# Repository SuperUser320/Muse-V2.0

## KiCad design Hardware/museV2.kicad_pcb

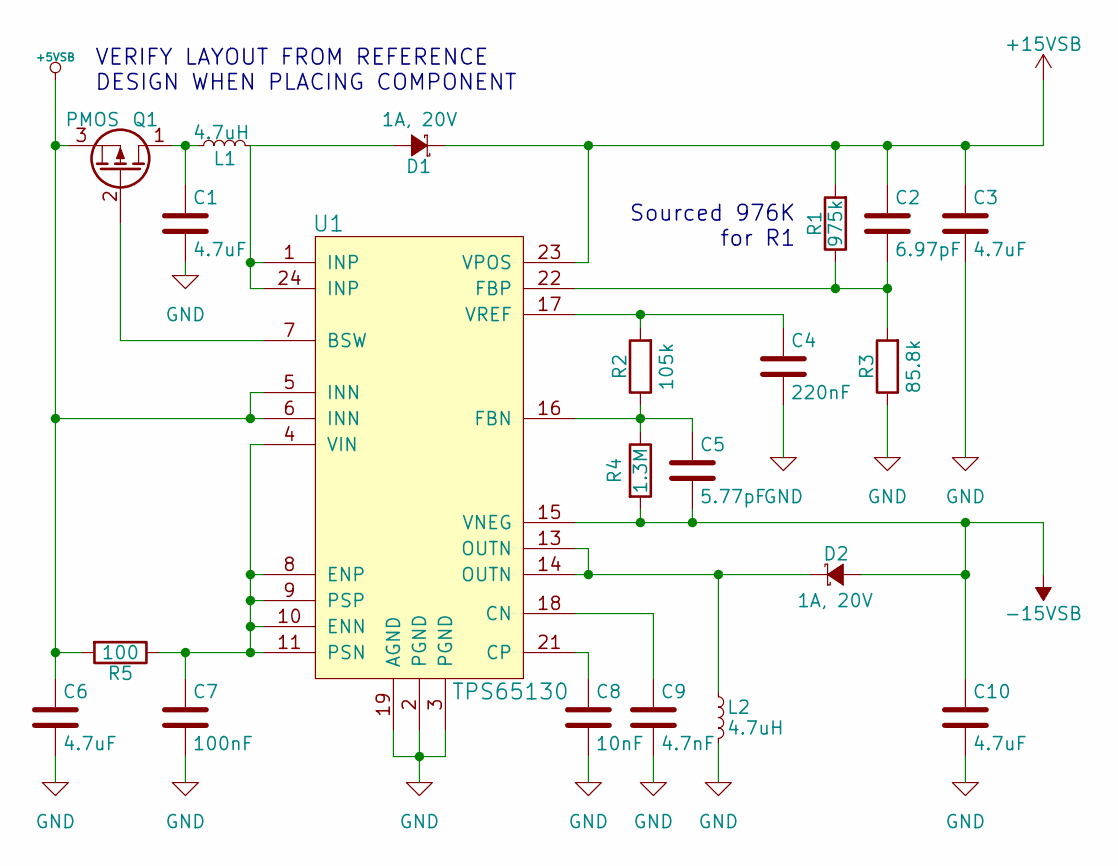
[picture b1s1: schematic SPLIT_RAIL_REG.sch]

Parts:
C1, C6: 4.7uF; C_0603
C2: 6.97pF; C_0402
C3, C10: 4.7uF; C_1206
C4: 220nF; C_0603
C5: 5.77pF; C_0603
C7: 100nF; C_0603
C8: 10nF; C_0603
C9: 4.7nF; C_0603
D1, D2: 1A, 20V; DO-216-AA
L1, L2: 4.7uH; 7.3mm-Inductor
Q1: PMOS; SOT-23
R1: 975k; R_0402
R2: 105k; R_0402
R3: 85.8k; R_0402
R4: 1.3M; R_0402
R5: 100; R_0402
U1: TPS65130; QFN-24-1EP_4x4mm_Pitch0.5mm_THERMAL

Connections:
+5VSB: C6.1, Q1.3 (S), R5.2, U1.5 (INN), U1.6 (INN); also elsewhere on the board
+15V: C2.1, C3.1, D1.1 (K), R1.2, U1.23 (VPOS); also elsewhere on the board
-15V: C5.2, C10.1, D2.2 (A), R4.2, U1.15 (VNEG); also elsewhere on the board
GND: C1.2, C3.2, C4.2, C6.2, C7.2, C8.2, C9.2, C10.2, L2.2, R3.1, U1.2 (PGND), U1.3 (PGND), U1.19 (AGND); also elsewhere on the board
unnamed: C1.1, L1.1, Q1.1 (D)
unnamed: C2.2, R1.1, R3.2, U1.22 (FBP)
unnamed: C4.1, R2.2, U1.17 (VREF)
unnamed: C5.1, R2.1, R4.1, U1.16 (FBN)
unnamed: C7.1, R5.1, U1.4 (VIN), U1.8 (ENP), U1.9 (PSP), U1.10 (ENN), U1.11 (PSN)
unnamed: C8.1, U1.21 (CP)
unnamed: C9.1, U1.18 (CN)
unnamed: D1.2 (A), L1.2, U1.1 (INP), U1.24 (INP)
unnamed: D2.1 (K), L2.1, U1.13 (OUTN), U1.14 (OUTN)
unnamed: Q1.2 (G), U1.7 (BSW)

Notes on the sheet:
VERIFY LAYOUT FROM REFERENCE DESIGN WHEN PLACING COMPONENT
Sourced 976K for R1

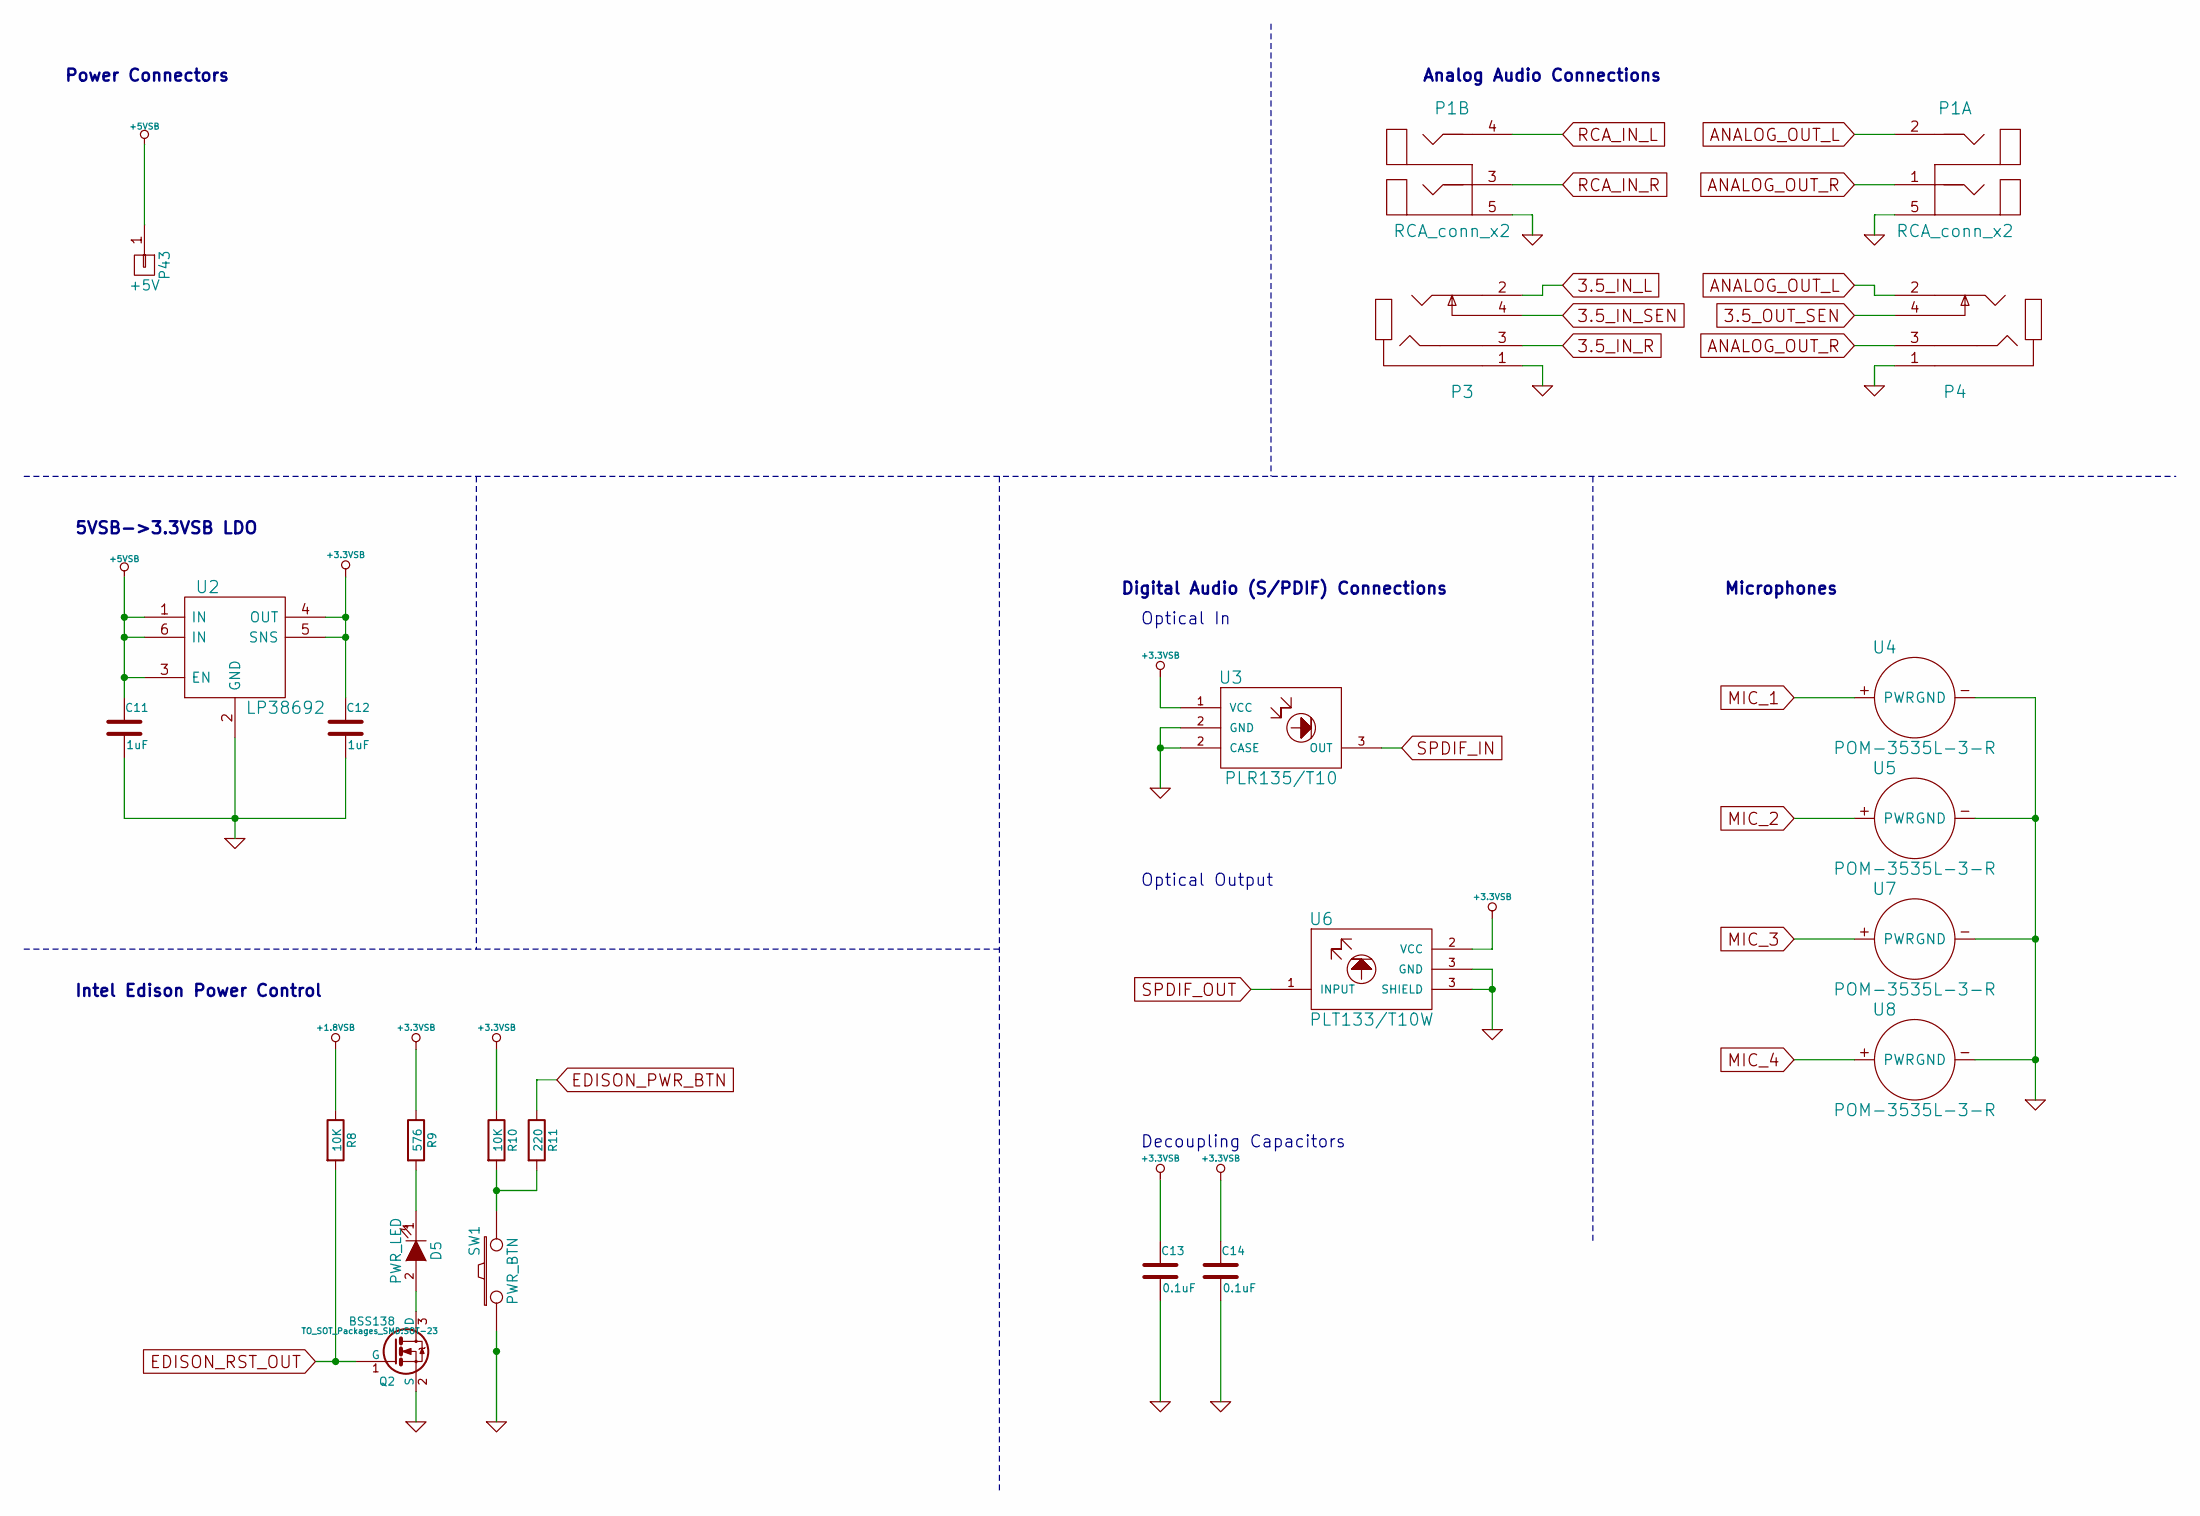
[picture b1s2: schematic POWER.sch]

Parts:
C11, C12: 1uF; C_0402
C13, C14: 0.1uF; C_0402
D5: PWR_LED; LED_0805
P1: RCA_conn_x2; PJRAS2X2S01X
P3, P4: 3.5mm_conn_tip_switch; 3.5MM-AUDIO-SMD
P43: +5V; Pin_Header_Straight_1x01
Q2: BSS138; SOT-23
R8, R10: 10K; R_0402
R9: 576; R_0402
R11: 220; R_0402
SW1: PWR_BTN; MF_Switches-TACT4.2MM
U2: LP38692; WSON6
U3: PLR135/T10; PLT133-T10W
U4, U5, U7, U8: POM-3535L-3-R; Pin_Header_Straight_1x02_MIC
U6: PLT133/T10W; PLT133-T10W

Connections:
3.5_IN_L: P3.2; also elsewhere on the board
3.5_IN_R: P3.3; also elsewhere on the board
3.5_IN_SEN: P3.4
3.5_OUT_SEN: P4.4
+1.8VSB: R8.1; also elsewhere on the board
+3.3VSB: C12.1, C13.1, C14.1, R9.1, R10.1, U2.4 (OUT), U2.5 (SNS), U3.1 (VCC), U6.2 (VCC); also elsewhere on the board
+5VSB: C11.1, P43.1, U2.1 (IN), U2.3 (EN), U2.6 (IN); also elsewhere on the board
ANALOG_OUT_L: P1.2, P4.2; also elsewhere on the board
ANALOG_OUT_R: P1.1, P4.3; also elsewhere on the board
EDISON_PWR_BTN: R11.1; also elsewhere on the board
EDISON_RST_OUT: Q2.1 (G), R8.2; also elsewhere on the board
GND: C11.2, C12.2, C13.2, C14.2, P1.5, P3.1, P4.1, Q2.2 (S), SW1.1, U2.2 (GND), U3.2 (CASE), U4.- (GND), U5.- (GND), U6.3 (GND), U7.- (GND), U8.- (GND); also elsewhere on the board
MIC_1: U4.+ (PWR); also elsewhere on the board
MIC_2: U5.+ (PWR); also elsewhere on the board
MIC_3: U7.+ (PWR); also elsewhere on the board
MIC_4: U8.+ (PWR); also elsewhere on the board
unnamed: D5.1 (K), R9.2
unnamed: D5.2 (A), Q2.3 (D)
unnamed: R10.2, R11.2, SW1.2
RCA_IN_L: P1.4; also elsewhere on the board
RCA_IN_R: P1.3; also elsewhere on the board
SPDIF_IN: U3.3 (OUT); also elsewhere on the board
SPDIF_OUT: U6.1 (INPUT); also elsewhere on the board

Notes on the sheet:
Intel Edison Power Control
5VSB->3.3VSB LDO
Power Connectors
Optical Output
Optical In
Digital Audio (S/PDIF) Connections
Analog Audio Connections
Microphones
Decoupling Capacitors

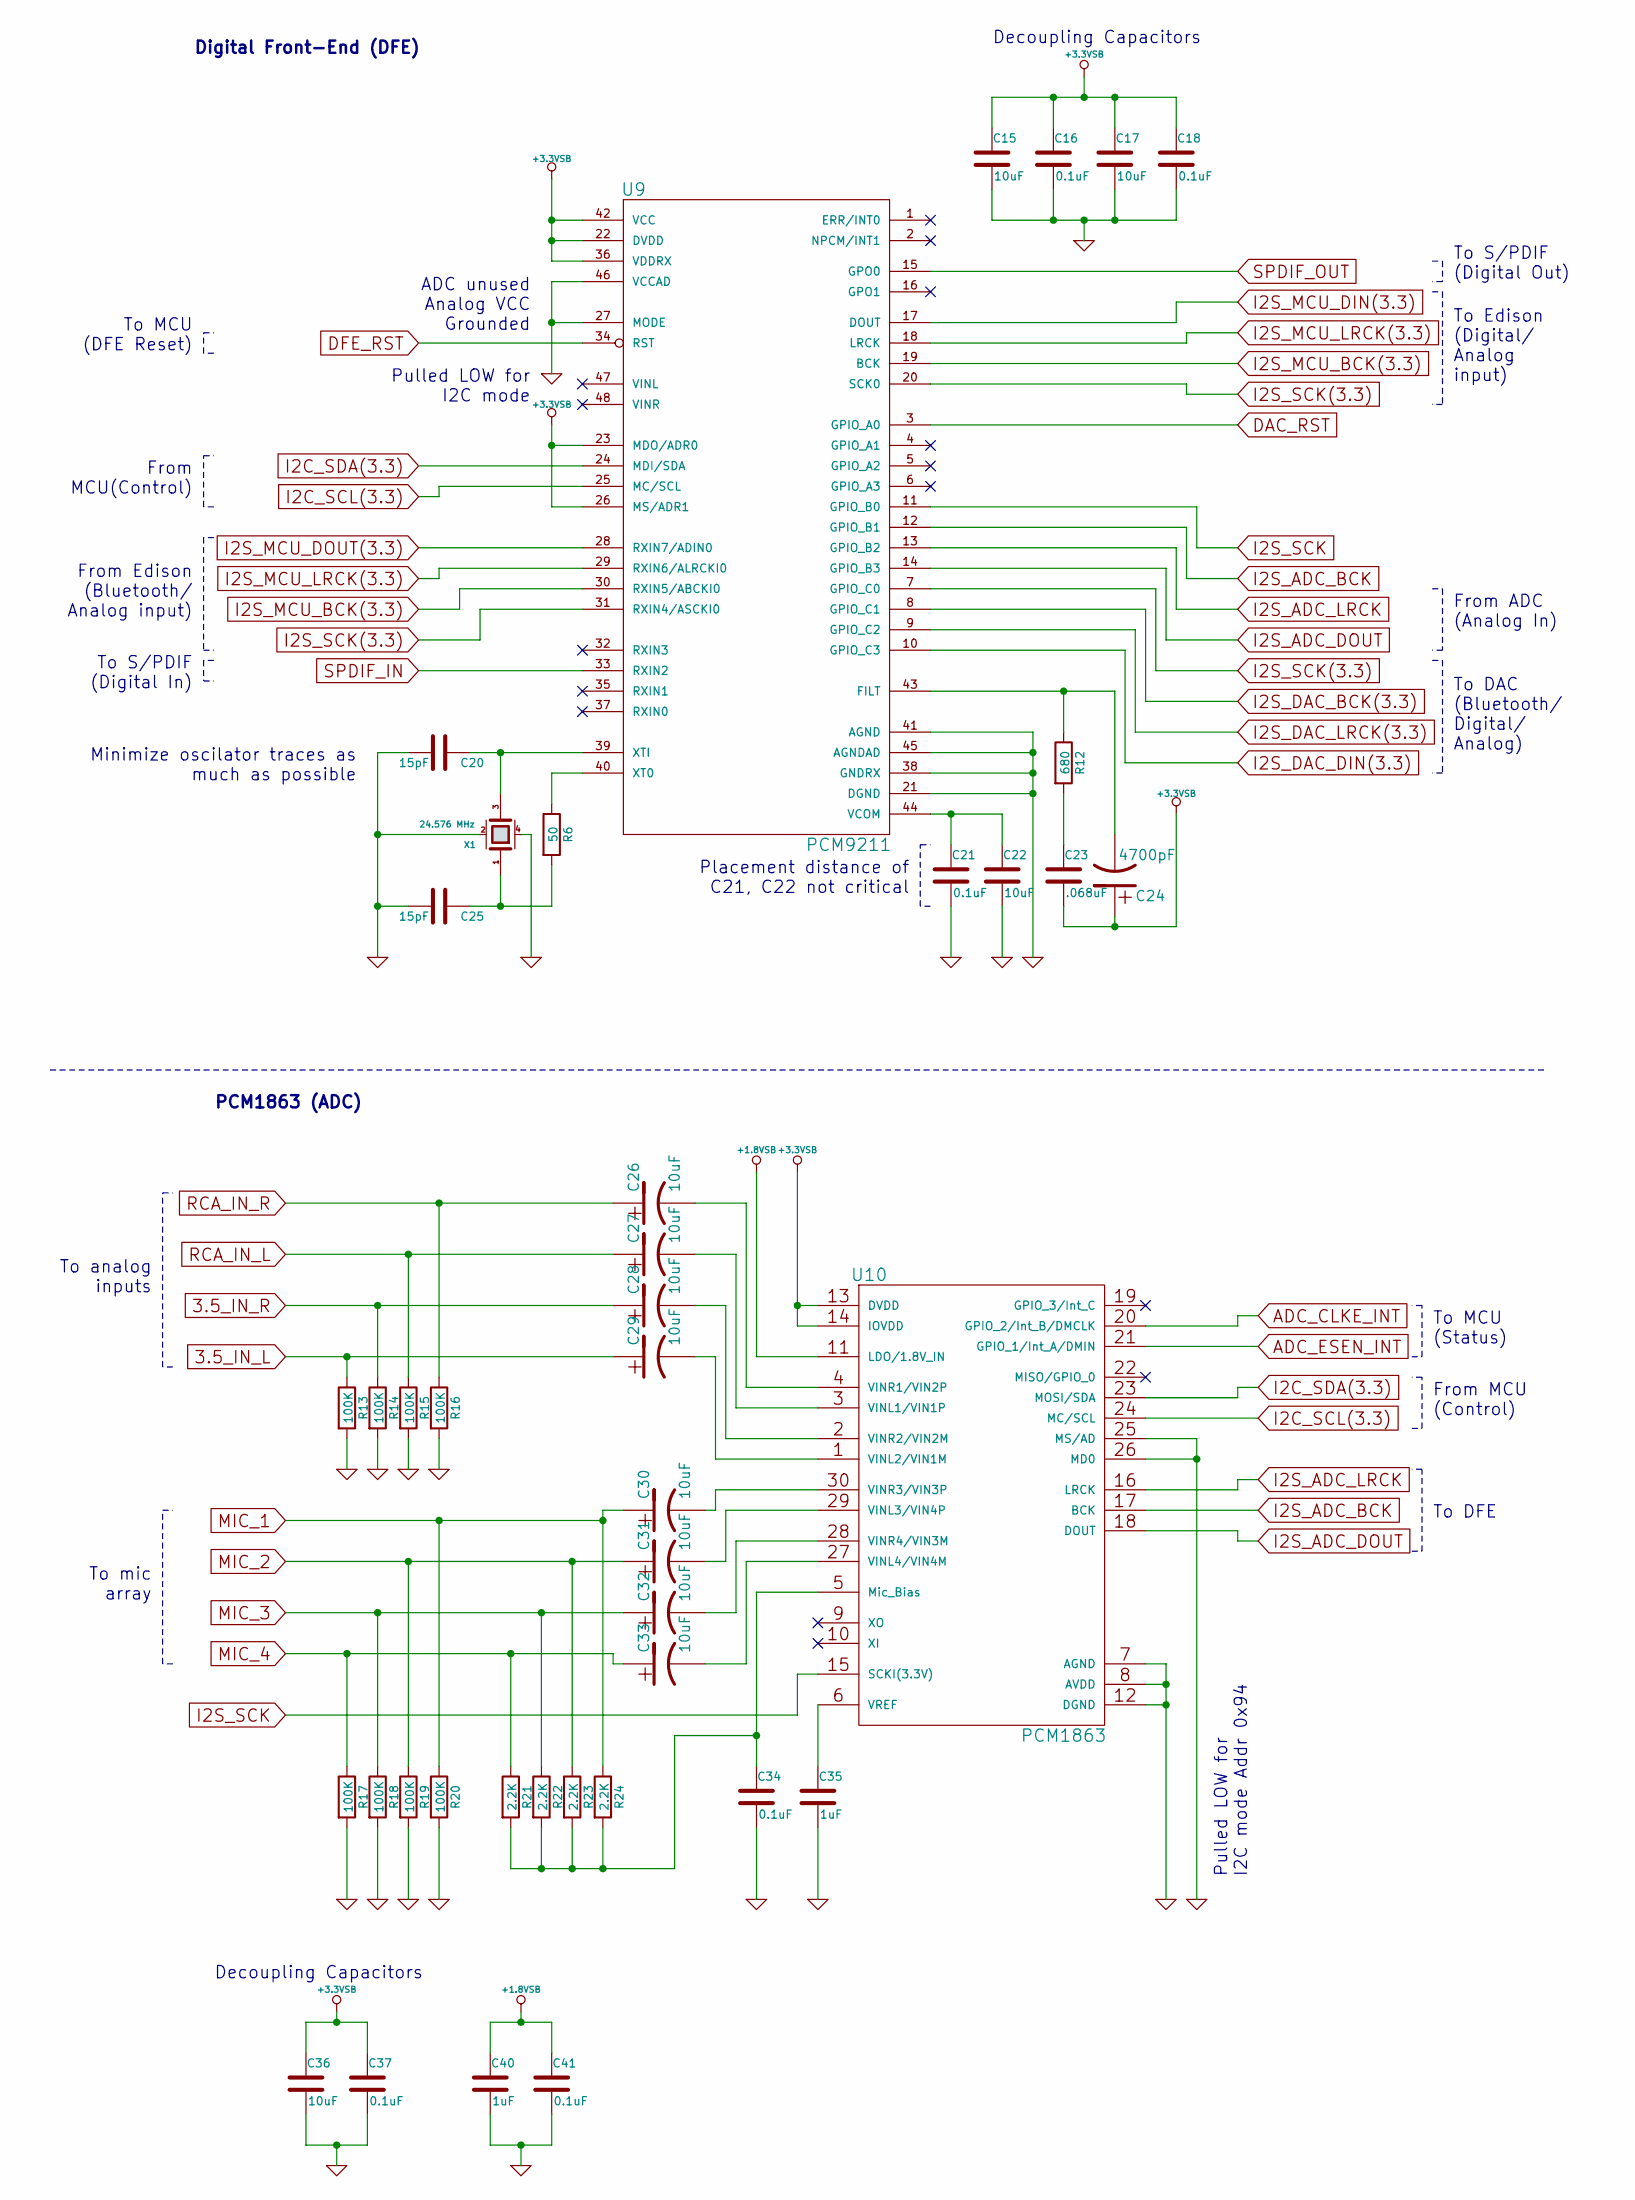
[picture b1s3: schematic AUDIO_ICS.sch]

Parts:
C15, C17, C22, C26, C27, C28, C29, C30, C31, C32, C33, C36: 10uF; c_elec_4x5.3
C16, C18, C21, C34, C37, C41: 0.1uF; C_0402
C20, C25: 15pF; C_0402
C23: .068uF; C_0402
C24: 4700pF; C_0805
C35: 1uF; C_0402
C40: 1uF; C_0603
R6: 50; R_0402
R12: 680; R_0402
R13, R14, R15, R16, R17, R18, R19, R20: 100K; R_0402
R21, R22, R23, R24: 2.2K; R_0402
U9: PCM9211; LQFP-48_7x7mm_Pitch0.5mm
U10: PCM1863; TSSOP-30_4.1x7.8mm_Pitch0.5mm
X1: 24.576 MHz; 5x3.2mm_crystal

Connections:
3.5_IN_L: C29.1, R13.1; also elsewhere on the board
3.5_IN_R: C28.1, R14.1; also elsewhere on the board
+1.8VSB: C40.1, C41.1, U10.11 (LDO/1.8V_IN); also elsewhere on the board
+3.3VSB: C15.1, C16.1, C17.1, C18.1, C23.2, C24.1, C36.1, C37.1, U9.22 (DVDD), U9.23 (MDO/ADR0), U9.26 (MS/ADR1), U9.36 (VDDRX), U9.42 (VCC), U10.13 (DVDD), U10.14 (IOVDD); also elsewhere on the board
ADC_CLKE_INT: U10.20 (GPIO_2/Int_B/DMCLK); also elsewhere on the board
ADC_ESEN_INT: U10.21 (GPIO_1/Int_A/DMIN); also elsewhere on the board
DAC_RST: U9.3 (GPIO_A0); also elsewhere on the board
DFE_RST: U9.34 (RST); also elsewhere on the board
GND: C15.2, C16.2, C17.2, C18.2, C20.2, C21.2, C22.2, C25.2, C34.2, C35.2, C36.2, C37.2, C40.2, C41.2, R13.2, R14.2, R15.2, R16.2, R17.2, R18.2, R19.2, R20.2, U9.21 (DGND), U9.27 (MODE), U9.38 (GNDRX), U9.41 (AGND), U9.45 (AGNDAD), U9.46 (VCCAD), U10.7 (AGND), U10.8 (AVDD), U10.12 (DGND), U10.25 (MS/AD), U10.26 (MD0), X1.2 (case), X1.4 (VDD); also elsewhere on the board
I2C_SCL(3.3): U9.25 (MC/SCL), U10.24 (MC/SCL); also elsewhere on the board
I2C_SDA(3.3): U9.24 (MDI/SDA), U10.23 (MOSI/SDA); also elsewhere on the board
I2S_ADC_BCK: U9.12 (GPIO_B1), U10.17 (BCK)
I2S_ADC_DOUT: U9.14 (GPIO_B3), U10.18 (DOUT)
I2S_ADC_LRCK: U9.13 (GPIO_B2), U10.16 (LRCK)
I2S_DAC_BCK(3.3): U9.8 (GPIO_C1); also elsewhere on the board
I2S_DAC_DIN(3.3): U9.10 (GPIO_C3); also elsewhere on the board
I2S_DAC_LRCK(3.3): U9.9 (GPIO_C2); also elsewhere on the board
I2S_MCU_BCK(3.3): U9.19 (BCK), U9.30 (RXIN5/ABCKI0); also elsewhere on the board
I2S_MCU_DIN(3.3): U9.17 (DOUT); also elsewhere on the board
I2S_MCU_DOUT(3.3): U9.28 (RXIN7/ADIN0); also elsewhere on the board
I2S_MCU_LRCK(3.3): U9.18 (LRCK), U9.29 (RXIN6/ALRCKI0); also elsewhere on the board
I2S_SCK: U9.11 (GPIO_B0), U10.15 (SCKI(3.3V))
I2S_SCK(3.3): U9.7 (GPIO_C0), U9.20 (SCK0), U9.31 (RXIN4/ASCKI0); also elsewhere on the board
MIC_1: C30.1, R20.1, R24.1; also elsewhere on the board
MIC_2: C31.1, R19.1, R23.1; also elsewhere on the board
MIC_3: C32.1, R18.1, R22.1; also elsewhere on the board
MIC_4: C33.1, R17.1, R21.1; also elsewhere on the board
unnamed: C20.1, U9.39 (XTI), X1.3 (out)
unnamed: C21.1, C22.1, U9.44 (VCOM)
unnamed: C23.1, R12.2
unnamed: C24.2, R12.1, U9.43 (FILT)
unnamed: C25.1, R6.2, X1.1 (ctl)
unnamed: C26.2, U10.4 (VINR1/VIN2P)
unnamed: C27.2, U10.3 (VINL1/VIN1P)
unnamed: C28.2, U10.2 (VINR2/VIN2M)
unnamed: C29.2, U10.1 (VINL2/VIN1M)
unnamed: C30.2, U10.30 (VINR3/VIN3P)
unnamed: C31.2, U10.29 (VINL3/VIN4P)
unnamed: C32.2, U10.28 (VINR4/VIN3M)
unnamed: C33.2, U10.27 (VINL4/VIN4M)
unnamed: C34.1, R21.2, R22.2, R23.2, R24.2, U10.5 (Mic_Bias)
unnamed: C35.1, U10.6 (VREF)
unnamed: R6.1, U9.40 (XT0)
RCA_IN_L: C27.1, R15.1; also elsewhere on the board
RCA_IN_R: C26.1, R16.1; also elsewhere on the board
SPDIF_IN: U9.33 (RXIN2); also elsewhere on the board
SPDIF_OUT: U9.15 (GPO0); also elsewhere on the board

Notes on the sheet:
From MCU(Control)
To S/PDIF (Digital Out)
From ADC (Analog In)
To DAC (Bluetooth/ Digital/ Analog)
To Edison (Digital/ Analog input)
Digital Front-End (DFE)
ADC unused Analog VCC Grounded
Pulled LOW for I2C mode
Pulled LOW for I2C mode Addr 0x94
PCM1863 (ADC)
From Edison (Bluetooth/ Analog input)
To S/PDIF (Digital In)
To mic array
To analog inputs
To DFE
From MCU (Control)
To MCU (Status)
To MCU (DFE Reset)
Decoupling Capacitors
Minimize oscilator traces as much as possible
Placement distance of C21, C22 not critical

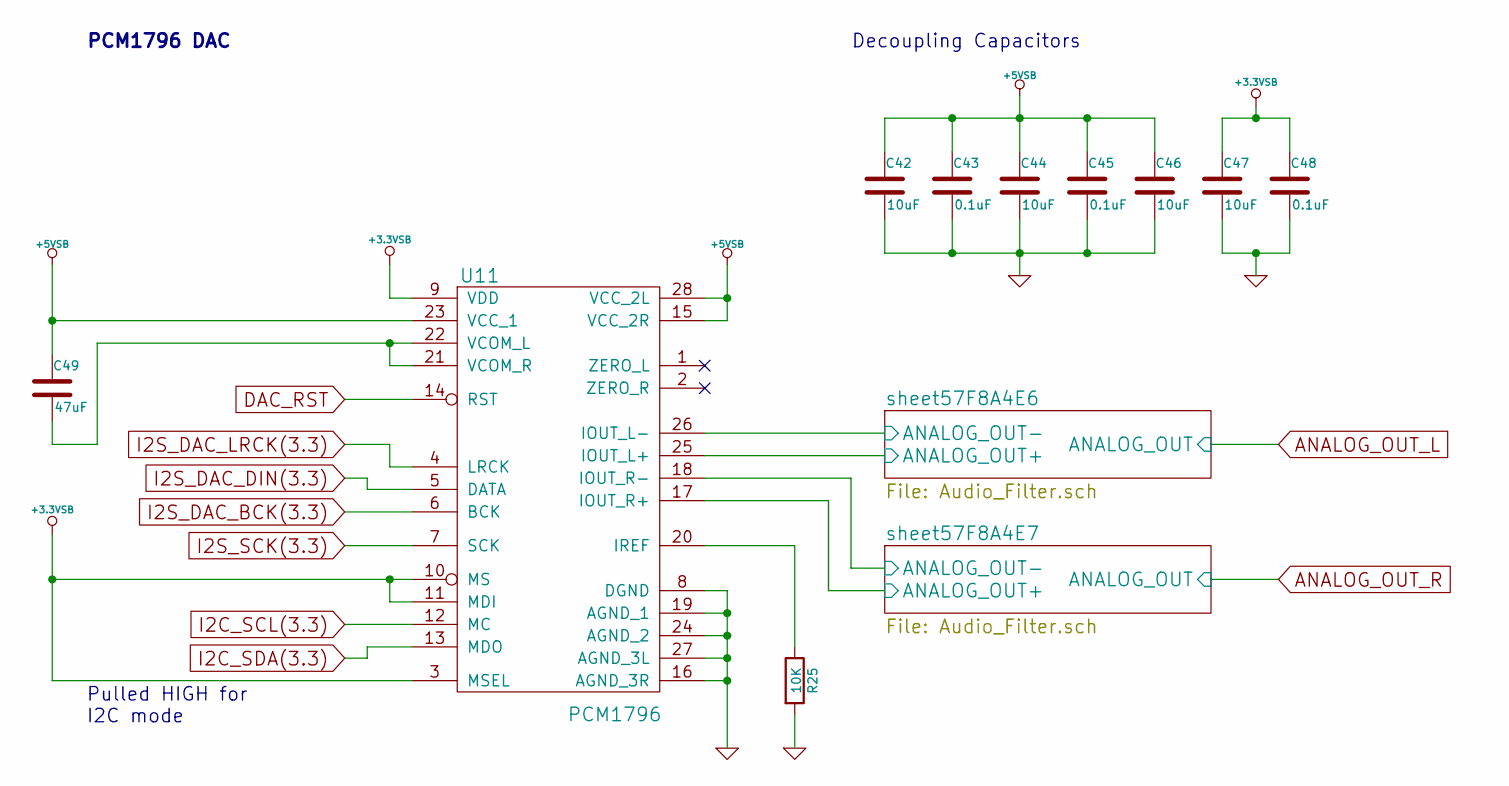
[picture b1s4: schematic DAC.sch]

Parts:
C42, C44, C46: 10uF; c_elec_4x4.5
C43, C45, C48: 0.1uF; C_0402
C47: 10uF; C_1206
C49: 47uF; c_elec_6.3x7.7
R25: 10K; R_0402
U11: PCM1796; SSOP-28_5.3x10.2mm_Pitch0.65mm

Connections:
+3.3VSB: C47.1, C48.1, U11.3 (MSEL), U11.9 (VDD), U11.10 (MS), U11.11 (MDI); also elsewhere on the board
+5VSB: C42.1, C43.1, C44.1, C45.1, C46.1, C49.1, U11.15 (VCC_2R), U11.23 (VCC_1), U11.28 (VCC_2L); also elsewhere on the board
/DAC/sheet57F8A4E6/ANALOG_OUT+: U11.25 (IOUT_L+); also elsewhere on the board
/DAC/sheet57F8A4E6/ANALOG_OUT-: U11.26 (IOUT_L-); also elsewhere on the board
/DAC/sheet57F8A4E7/ANALOG_OUT+: U11.17 (IOUT_R+); also elsewhere on the board
/DAC/sheet57F8A4E7/ANALOG_OUT-: U11.18 (IOUT_R-); also elsewhere on the board
DAC_RST: U11.14 (RST); also elsewhere on the board
GND: C42.2, C43.2, C44.2, C45.2, C46.2, C47.2, C48.2, R25.2, U11.8 (DGND), U11.16 (AGND_3R), U11.19 (AGND_1), U11.24 (AGND_2), U11.27 (AGND_3L); also elsewhere on the board
I2C_SCL(3.3): U11.12 (MC); also elsewhere on the board
I2C_SDA(3.3): U11.13 (MDO); also elsewhere on the board
I2S_DAC_BCK(3.3): U11.6 (BCK); also elsewhere on the board
I2S_DAC_DIN(3.3): U11.5 (DATA); also elsewhere on the board
I2S_DAC_LRCK(3.3): U11.4 (LRCK); also elsewhere on the board
I2S_SCK(3.3): U11.7 (SCK); also elsewhere on the board
unnamed: C49.2, U11.21 (VCOM_R), U11.22 (VCOM_L)
unnamed: R25.1, U11.20 (IREF)

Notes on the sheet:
Pulled HIGH for I2C mode
Decoupling Capacitors
PCM1796 DAC

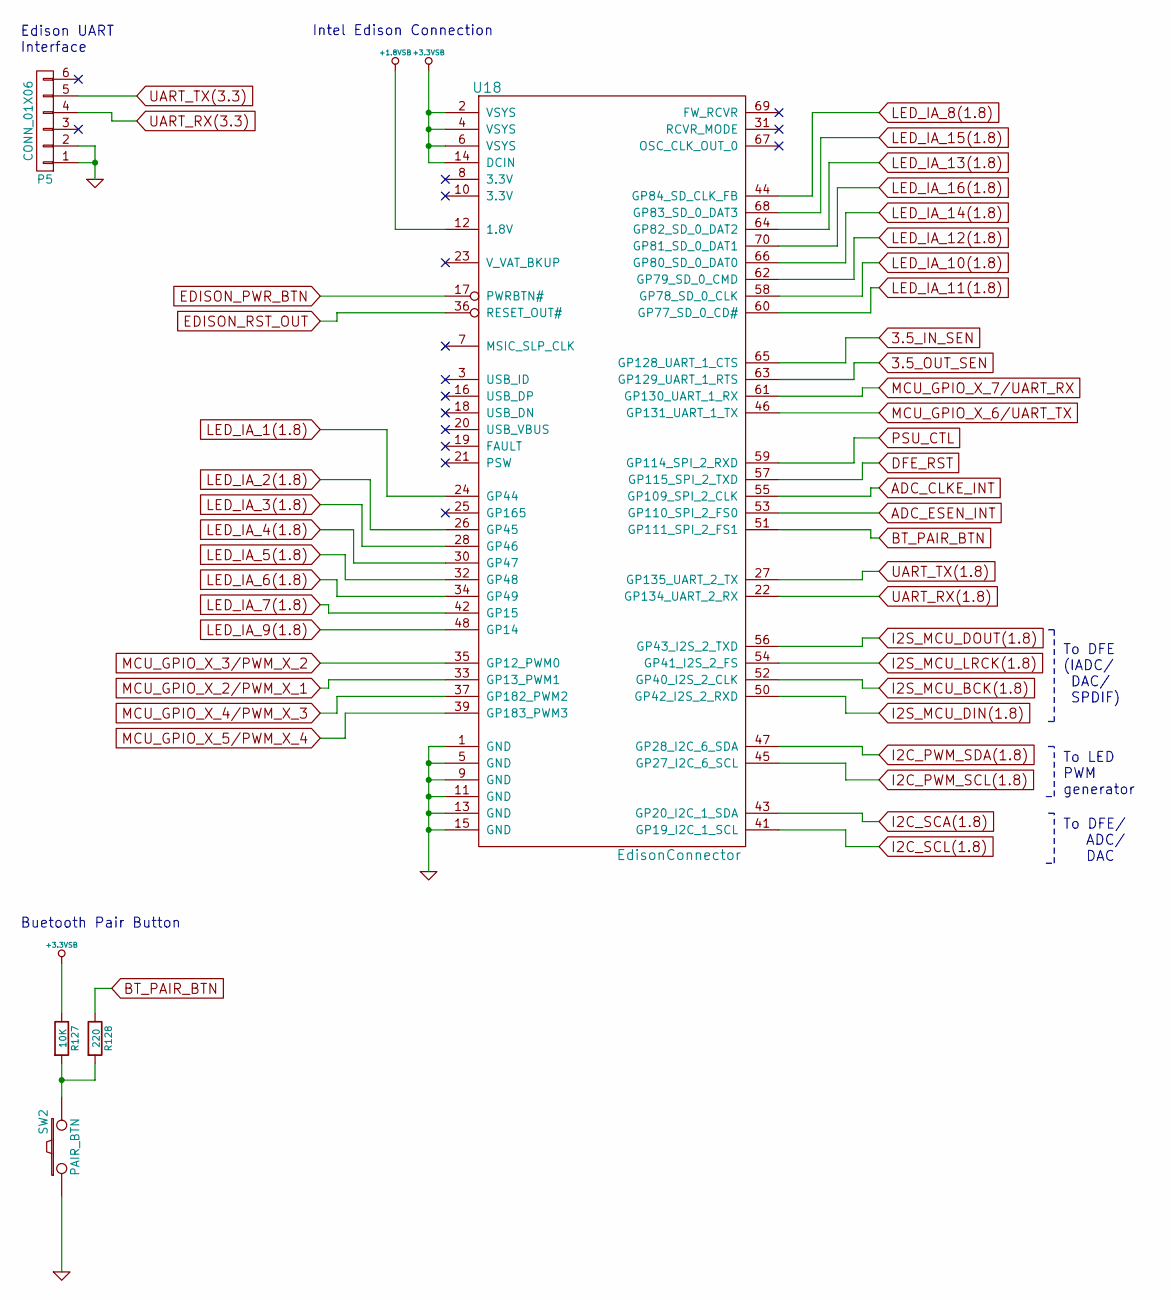
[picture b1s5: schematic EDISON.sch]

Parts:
P5: CONN_01X06; Pin_Header_Straight_1x06
R127: 10K; R_0402
R128: 220; R_0402
SW2: PAIR_BTN; MF_Switches-TACT4.2MM
U18: EdisonConnector; Intel_Edison

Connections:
+1.8VSB: U18.12 (1.8V); also elsewhere on the board
+3.3VSB: R127.1, U18.2 (VSYS), U18.4 (VSYS), U18.6 (VSYS), U18.14 (DCIN); also elsewhere on the board
ADC_CLKE_INT: U18.55 (GP109_SPI_2_CLK); also elsewhere on the board
ADC_ESEN_INT: U18.53 (GP110_SPI_2_FS0); also elsewhere on the board
BT_PAIR_BTN: R128.1, U18.51 (GP111_SPI_2_FS1)
DFE_RST: U18.57 (GP115_SPI_2_TXD); also elsewhere on the board
EDISON_PWR_BTN: U18.17 (PWRBTN#); also elsewhere on the board
EDISON_RST_OUT: U18.36 (RESET_OUT#); also elsewhere on the board
GND: P5.1, P5.2, SW2.1, U18.1 (GND), U18.5 (GND), U18.9 (GND), U18.11 (GND), U18.13 (GND), U18.15 (GND); also elsewhere on the board
I2C_PWM_SCL(1.8): U18.45 (GP27_I2C_6_SCL); also elsewhere on the board
I2C_PWM_SDA(1.8): U18.47 (GP28_I2C_6_SDA); also elsewhere on the board
I2C_SCA(1.8): U18.43 (GP20_I2C_1_SDA); also elsewhere on the board
I2C_SCL(1.8): U18.41 (GP19_I2C_1_SCL); also elsewhere on the board
I2S_MCU_BCK(1.8): U18.52 (GP40_I2S_2_CLK); also elsewhere on the board
I2S_MCU_DIN(1.8): U18.50 (GP42_I2S_2_RXD); also elsewhere on the board
I2S_MCU_DOUT(1.8): U18.56 (GP43_I2S_2_TXD); also elsewhere on the board
I2S_MCU_LRCK(1.8): U18.54 (GP41_I2S_2_FS); also elsewhere on the board
LED_IA_1(1.8): U18.24 (GP44); also elsewhere on the board
LED_IA_2(1.8): U18.26 (GP45); also elsewhere on the board
LED_IA_3(1.8): U18.28 (GP46); also elsewhere on the board
LED_IA_4(1.8): U18.30 (GP47); also elsewhere on the board
LED_IA_5(1.8): U18.32 (GP48); also elsewhere on the board
LED_IA_6(1.8): U18.34 (GP49); also elsewhere on the board
LED_IA_7(1.8): U18.42 (GP15); also elsewhere on the board
LED_IA_8(1.8): U18.44 (GP84_SD_CLK_FB); also elsewhere on the board
LED_IA_9(1.8): U18.48 (GP14); also elsewhere on the board
LED_IA_10(1.8): U18.58 (GP78_SD_0_CLK); also elsewhere on the board
LED_IA_11(1.8): U18.60 (GP77_SD_0_CD#); also elsewhere on the board
LED_IA_12(1.8): U18.62 (GP79_SD_0_CMD); also elsewhere on the board
LED_IA_13(1.8): U18.64 (GP82_SD_0_DAT2); also elsewhere on the board
LED_IA_14(1.8): U18.66 (GP80_SD_0_DAT0); also elsewhere on the board
LED_IA_15(1.8): U18.68 (GP83_SD_0_DAT3); also elsewhere on the board
LED_IA_16(1.8): U18.70 (GP81_SD_0_DAT1); also elsewhere on the board
MCU_GPIO_X_2/PWM_X_1: U18.33 (GP13_PWM1); also elsewhere on the board
MCU_GPIO_X_3/PWM_X_2: U18.35 (GP12_PWM0); also elsewhere on the board
MCU_GPIO_X_4/PWM_X_3: U18.37 (GP182_PWM2); also elsewhere on the board
MCU_GPIO_X_5/PWM_X_4: U18.39 (GP183_PWM3)
MCU_GPIO_X_6/UART_TX: U18.46 (GP131_UART_1_TX); also elsewhere on the board
MCU_GPIO_X_7/UART_RX: U18.61 (GP130_UART_1_RX); also elsewhere on the board
unnamed: R127.2, R128.2, SW2.2
PSU_CTL: U18.59 (GP114_SPI_2_RXD); also elsewhere on the board
UART_RX(1.8): U18.22 (GP134_UART_2_RX); also elsewhere on the board
UART_RX(3.3): P5.4; also elsewhere on the board
UART_TX(1.8): U18.27 (GP135_UART_2_TX); also elsewhere on the board
UART_TX(3.3): P5.5; also elsewhere on the board

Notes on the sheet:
To DFE (IADC/ DAC/ SPDIF)
Edison UART Interface
Intel Edison Connection
To DFE/ ADC/ DAC
To LED PWM generator
Buetooth Pair Button
